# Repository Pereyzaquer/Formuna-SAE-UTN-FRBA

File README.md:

# Fórmula SAE - UTN-FRBA

<p>Este repositorio está destinado al equipo de <strong>Fórmula SAE UTN-FRBA</strong>.<br>
Su objetivo es centralizar y compartir los <strong>esquemáticos</strong>, <strong>código</strong> y <strong>documentación técnica</strong> correspondientes a las distintas áreas del proyecto.</p>

<p>Para consultas, dudas o reportes de problemas, comuníquese con el responsable del área correspondiente.</p>

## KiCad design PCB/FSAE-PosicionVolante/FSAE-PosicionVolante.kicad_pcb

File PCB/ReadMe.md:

# Organización del repositorio

Para mantener un orden y facilitar el trabajo colaborativo, se recomienda seguir las siguientes pautas:

1. **Crear una carpeta por proyecto**, con un nombre descriptivo, para mantener separados los distintos desarrollos.

2. Colocar un ReadMe.md con la organizacion de la carpeta y los integrantes involucrados
3. **Coordinar con el resto del equipo** antes de realizar cambios importantes, para asegurar una correcta integración y evitar conflictos.
4. **Centralizar los símbolos y huellas** en dos carpetas específicas:
   - `Formula_SAE_FP`: destinada a guardar todos los **footprints (huellas)** creados o agregados.  
   - `Formula_SAE_SIM`: destinada a guardar todos los **símbolos esquemáticos** creados o agregados.

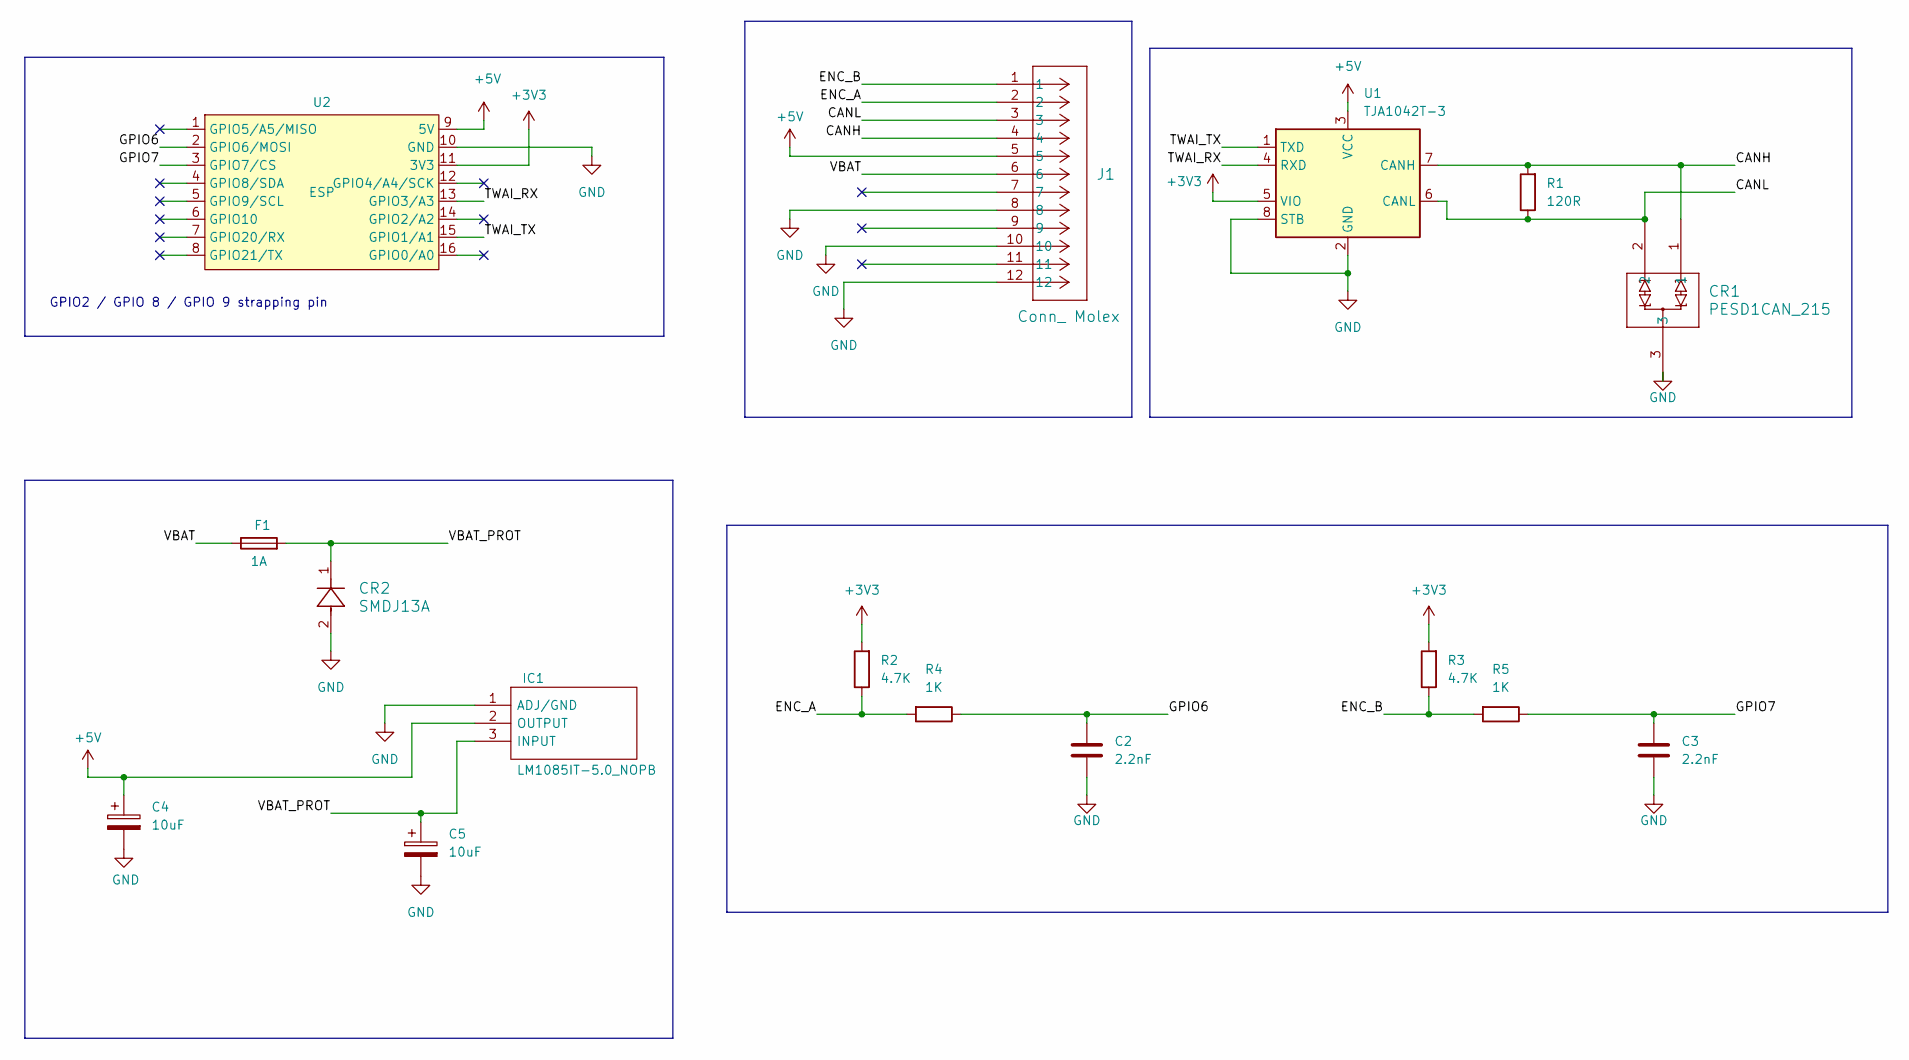
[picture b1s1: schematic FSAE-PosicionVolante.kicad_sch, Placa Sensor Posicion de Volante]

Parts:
C2, C3: 2.2nF; C_0805_2012Metric_Pad1.18x1.45mm_HandSolder
C4: 10uF; CP_EIA-3216-18_Kemet-A_HandSolder
C5: 10uF; C_1206_3216Metric_Pad1.33x1.80mm_HandSolder
CR1: PESD1CAN_215; SOT23_PESD1_NEX
CR2: SMDJ13A; SMDJSeries_LTF
F1: 1A; Fuse_1206_3216Metric_Pad1.42x1.75mm_HandSolder
IC1: LM1085IT-5.0_NOPB; TO254P470X1028X1955-3P; Manufacturer_Part_Number LM1085IT-5.0/NOPB
J1: Conn_ Molex; CONN_3678312xx_MOL
R1: 120R; R_0805_2012Metric_Pad1.20x1.40mm_HandSolder
R2, R3: 4.7K; R_0805_2012Metric_Pad1.20x1.40mm_HandSolder
R4, R5: 1K; R_0805_2012Metric_Pad1.20x1.40mm_HandSolder
U1: TJA1042T-3; SOIC-8_3.9x4.9mm_P1.27mm
U2: ESP; ESP32 C3 SM

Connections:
+3V3: R2.2, R3.2, U1.5 (VIO), U2.11 (3V3)
+5V: C4.1, IC1.2 (OUTPUT), J1.5, U1.3 (VCC), U2.9 (5V)
/CANH: CR1.1, J1.4, R1.2, U1.7 (CANH)
/CANL: CR1.2, J1.3, R1.1, U1.6 (CANL)
/ENC_A: J1.2, R2.1, R4.2
/ENC_B: J1.1, R3.1, R5.2
/GPIO6: C2.1, R4.1, U2.2 (GPIO6/MOSI)
/GPIO7: C3.1, R5.1, U2.3 (GPIO7/CS)
/TWAI_RX: U1.4 (RXD), U2.13 (GPIO3/A3)
/TWAI_TX: U1.1 (TXD), U2.15 (GPIO1/A1)
/VBAT: F1.1, J1.6
/VBAT_PROT: C5.1, CR2.1, F1.2, IC1.3 (INPUT)
GND: C2.2, C3.2, C4.2, C5.2, CR1.3, CR2.2, IC1.1 (ADJ/GND), J1.8, J1.10, J1.12, U1.2 (GND), U1.8 (STB), U2.10 (GND)

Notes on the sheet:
GPIO2 / GPIO 8 / GPIO 9 strapping pin

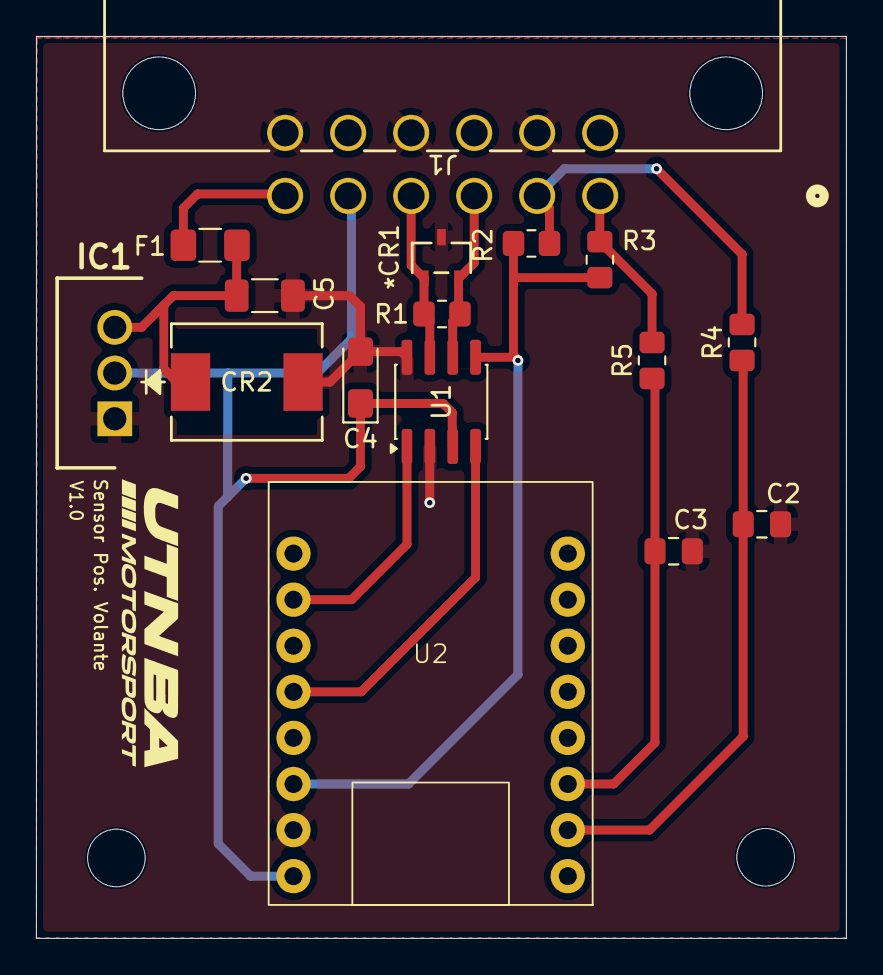
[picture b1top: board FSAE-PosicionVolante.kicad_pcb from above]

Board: 2 copper layers, 45.0 x 50.1 mm, 17 parts (0 on the bottom side), 13 nets.

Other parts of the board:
G: LOGO; logo

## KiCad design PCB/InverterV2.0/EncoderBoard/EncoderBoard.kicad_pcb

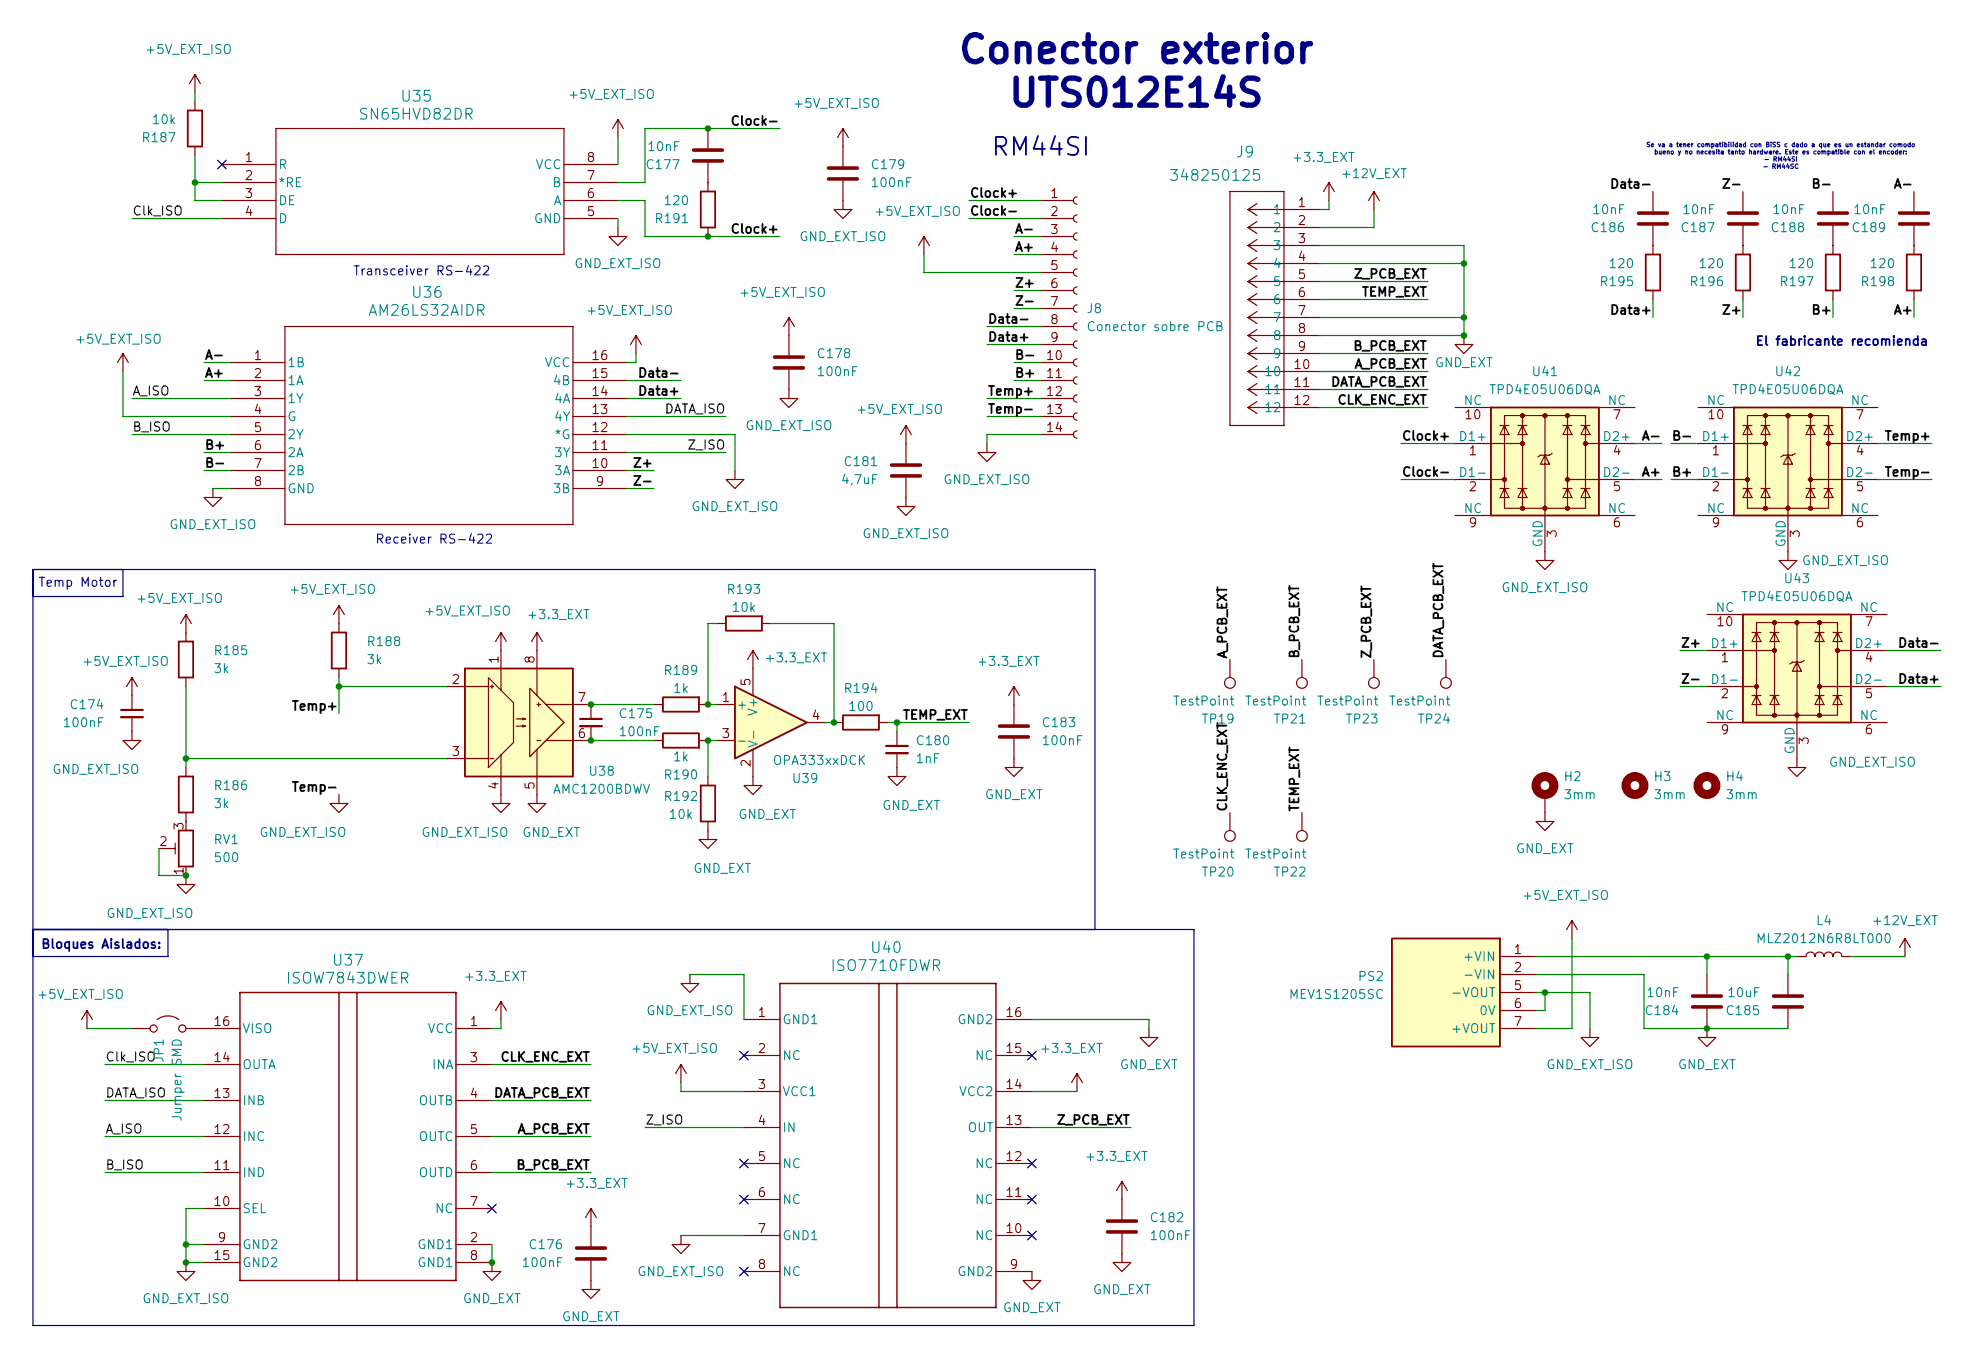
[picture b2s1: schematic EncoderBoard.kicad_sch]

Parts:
C174, C175, C176, C178, C179, C182, C183: 100nF; C_0603_1608Metric
C177, C184, C186, C187, C188, C189: 10nF; C_0603_1608Metric
C180: 1nF; C_0603_1608Metric
C181: 4,7uF; C_0805_2012Metric
C185: 10uF; C_0805_2012Metric
H2: 3mm; MountingHole_3.2mm_M3_ISO14580_Pad_TopBottom
H3, H4: 3mm; MountingHole_3.2mm_M3
J8: Conector sobre PCB; My-UTS012E14S
J9: 348250125; CONN_SD-34825-001_12_MOL
JP1: Jumper SMD; SolderJumper-2_P1.3mm_Open_RoundedPad1.0x1.5mm
L4: MLZ2012N6R8LT000; L_0805_2012Metric
PS2: MEV1S1205SC; MANUFACTURER_PART_NUMBER MEV1S1205SC; Mouser Part Number 580-MEV1S1205SC
R185, R186, R188: 3k; R_0603_1608Metric
R187: 10k; R_0603_1608Metric
R189, R190: 1k; R_0402_1005Metric
R191, R195, R196, R197, R198: 120; R_0603_1608Metric
R192, R193: 10k; R_0402_1005Metric
R194: 100; R_0402_1005Metric
RV1: 500; Potentiometer_Bourns_3296W_Vertical
TP19, TP20, TP21, TP22, TP23, TP24: TestPoint; TestPoint_Pad_D1.0mm
U35: SN65HVD82DR; D8_TEX-L
U36: AM26LS32AIDR; D16-L
U37: ISOW7843DWER; DWE0016A
U38: AMC1200BDWV; SOIC-8_7.5x5.85mm_P1.27mm
U39: OPA333xxDCK; SOT-353_SC-70-5
U40: ISO7710FDWR; SOIC16_DW_TEX-L
U41, U42, U43: TPD4E05U06DQA; USON-10_2.5x1.0mm_P0.5mm

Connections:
+3.3_EXT: C176.1, C182.1, C183.1, J9.1, U37.1 (VCC), U38.8 (VDD2), U39.5 (V+), U40.14 (VCC2)
+5V_EXT_ISO: C174.1, C178.1, C179.1, C181.1, J8.5, JP1.2 (B), PS2.7 (+VOUT), R185.2, R187.2, R188.2, U35.8 (VCC), U36.4 (G), U36.16 (VCC), U38.1 (VDD1), U40.3 (VCC1)
+12V_EXT: J9.2, L4.2
/A+: J8.4, R198.1, U36.2 (1A), U41.5 (D2-)
/A-: C189.1, J8.3, U36.1 (1B), U41.4 (D2+)
/A_ISO: U36.3 (1Y), U37.12 (INC)
/A_PCB_EXT: J9.10, TP19.1 (1_1), U37.5 (OUTC)
/B+: J8.11, R197.1, U36.6 (2A), U42.2 (D1-)
/B-: C188.1, J8.10, U36.7 (2B), U42.1 (D1+)
/B_ISO: U36.5 (2Y), U37.11 (IND)
/B_PCB_EXT: J9.9, TP21.1 (1_1), U37.6 (OUTD)
/CLK_ENC_EXT: J9.12, TP20.1 (1_1), U37.3 (INA)
/Clk_ISO: U35.4 (D), U37.14 (OUTA)
/Clock+: J8.1, R191.1, U35.6 (A), U41.1 (D1+)
/Clock-: C177.1, J8.2, U35.7 (B), U41.2 (D1-)
/DATA_ISO: U36.13 (4Y), U37.13 (INB)
/DATA_PCB_EXT: J9.11, TP24.1 (1_1), U37.4 (OUTB)
/Data+: J8.9, R195.1, U36.14 (4A), U43.5 (D2-)
/Data-: C186.1, J8.8, U36.15 (4B), U43.4 (D2+)
/TEMP_EXT: C180.1, J9.6, R194.2, TP22.1 (1_1)
/Temp+: J8.12, R188.1, U38.2 (VINP), U42.4 (D2+)
/Z+: J8.6, R196.1, U36.10 (3A), U43.1 (D1+)
/Z-: C187.1, J8.7, U36.9 (3B), U43.2 (D1-)
/Z_ISO: U36.11 (3Y), U40.4 (IN)
/Z_PCB_EXT: J9.5, TP23.1 (1_1), U40.13 (OUT)
GND_EXT: C176.2, C180.2, C182.2, C183.2, C184.2, C185.2, H2.1 (1_1), J9.3, J9.4, J9.7, J9.8, PS2.2 (-VIN), R192.1, U37.2 (GND1), U37.8 (GND1), U38.5 (GND2), U39.2 (V-), U40.9 (GND2), U40.16 (GND2)
GND_EXT_ISO: C174.2, C178.2, C179.2, C181.2, J8.13, J8.14, PS2.5 (-VOUT), PS2.6 (0V), RV1.1, RV1.2, U35.5 (GND), U36.8 (GND), U36.12 (*G), U37.9 (GND2), U37.10 (SEL), U37.15 (GND2), U38.4 (GND1), U40.1 (GND1), U40.7 (GND1), U41.3 (GND), U41.8 (GND), U42.3 (GND), U42.5 (D2-), U42.8 (GND), U43.3 (GND), U43.8 (GND)
unnamed: C177.2, R191.2
unnamed: C186.2, R195.2
unnamed: C187.2, R196.2
unnamed: C188.2, R197.2
unnamed: C189.2, R198.2
unnamed: JP1.1 (A), U37.16 (VISO)
unnamed: C184.1, C185.1, L4.1, PS2.1 (+VIN)
unnamed: R186.1, RV1.3
unnamed: R193.2, R194.1, U39.4
unnamed: R187.1, U35.2 (*RE), U35.3 (DE)
unnamed: R185.1, R186.2, U38.3 (VINN)
unnamed: C175.2, R190.1, U38.6 (VOUTN)
unnamed: C175.1, R189.1, U38.7 (VOUTP)
unnamed: R189.2, R193.1, U39.1 (+)
unnamed: R190.2, R192.2, U39.3 (-)

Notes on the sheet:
Conector exterior UTS012E14S
Receiver RS-422
Temp Motor
Transceiver RS-422
Se va a tener compatibilidad con BiSS c dado a que es un estandar comodo bueno y no necesita tanto hardware. Este es compatible con el encoder: - RM44SI - RM44SC
Bloques Aislados:
RM44SI
El fabricante recomienda

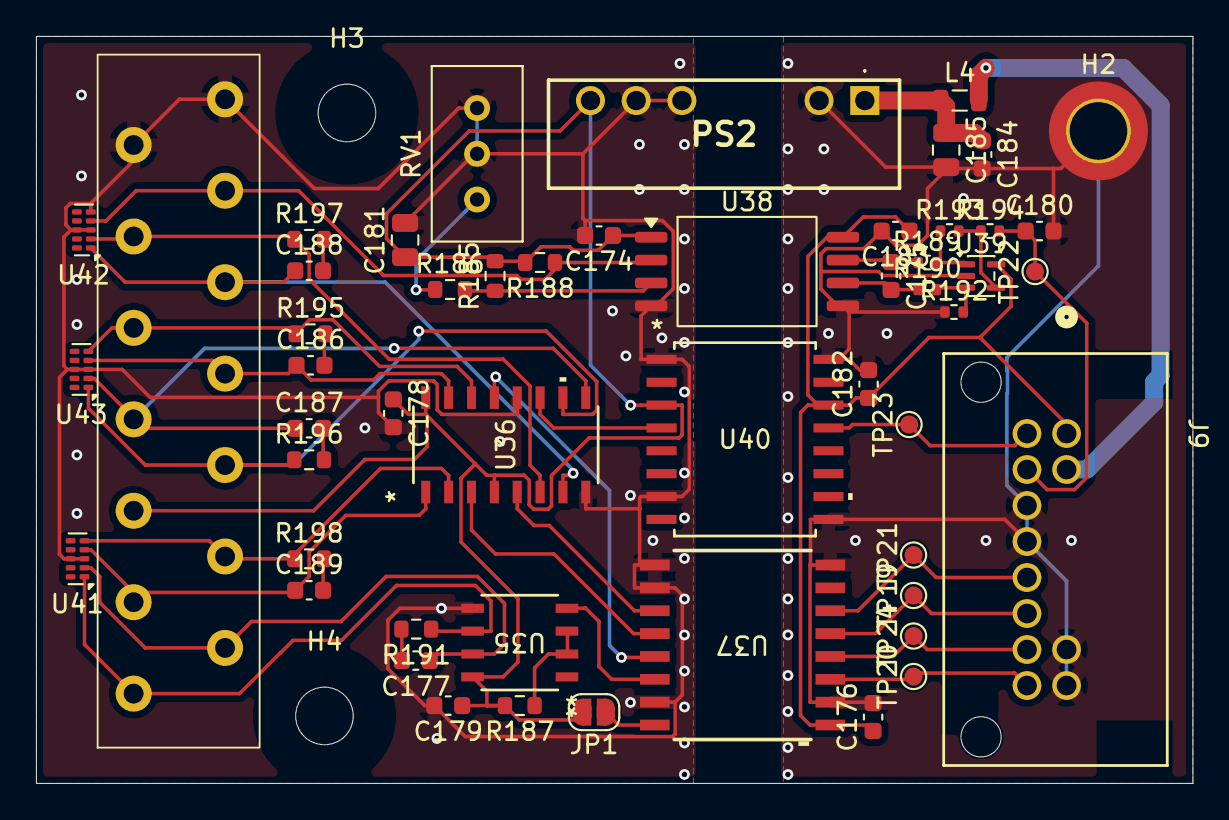
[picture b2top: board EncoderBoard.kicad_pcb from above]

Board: 2 copper layers, 64.2 x 41.5 mm, 54 parts (0 on the bottom side), 42 nets.

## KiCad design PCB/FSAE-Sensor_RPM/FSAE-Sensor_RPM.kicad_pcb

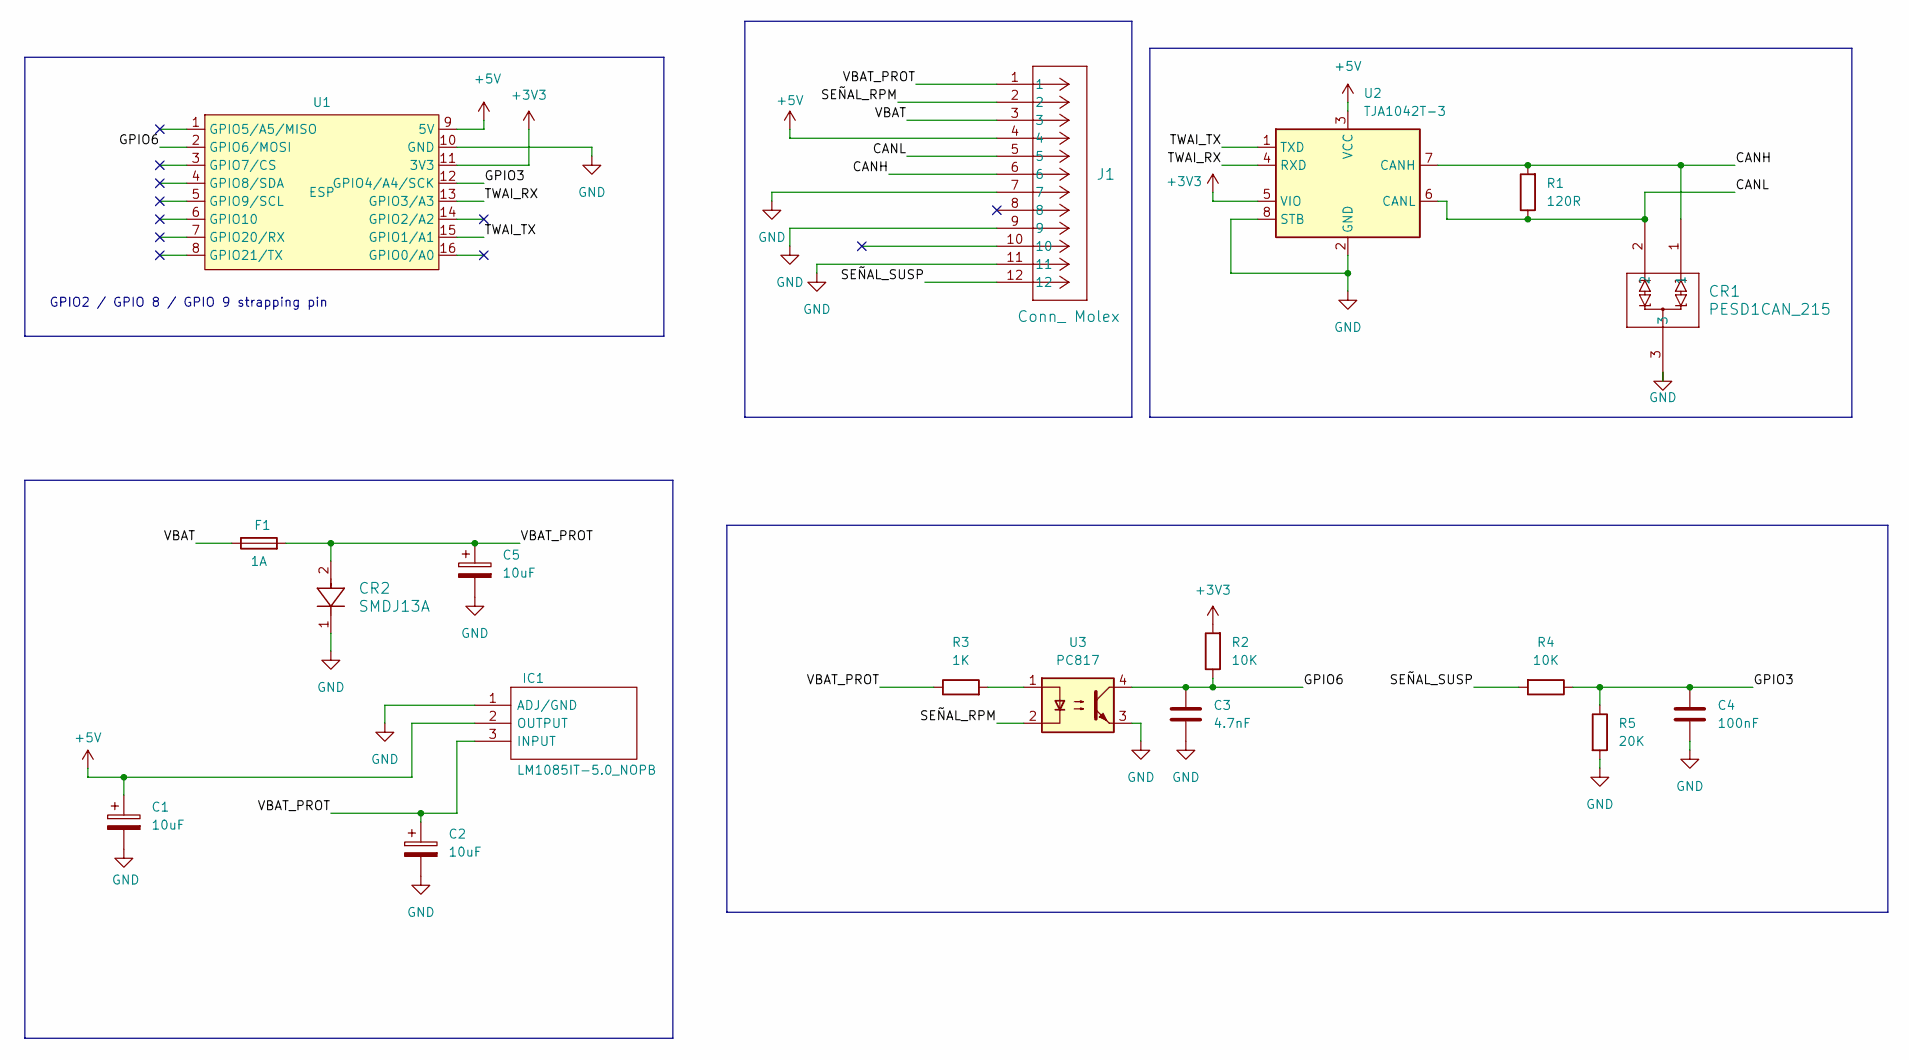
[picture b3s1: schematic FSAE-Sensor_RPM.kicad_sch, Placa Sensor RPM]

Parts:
C1: 10uF; CP_EIA-2012-12_Kemet-R_HandSolder
C2, C5: 10uF; C_0805_2012Metric_Pad1.18x1.45mm_HandSolder
C3: 4.7nF; C_0805_2012Metric_Pad1.18x1.45mm_HandSolder
C4: 100nF; C_0805_2012Metric_Pad1.18x1.45mm_HandSolder
CR1: PESD1CAN_215; SOT23_PESD1_NEX
CR2: SMDJ13A; SMDJSeries_LTF
F1: 1A; Fuse_1206_3216Metric_Pad1.42x1.75mm_HandSolder
IC1: LM1085IT-5.0_NOPB; TO254P470X1028X1955-3P; Manufacturer_Part_Number LM1085IT-5.0/NOPB
J1: Conn_ Molex; CONN_3678312xx_MOL
R1: 120R; R_0805_2012Metric_Pad1.20x1.40mm_HandSolder
R2, R4: 10K; R_0805_2012Metric_Pad1.20x1.40mm_HandSolder
R3: 1K; R_0805_2012Metric_Pad1.20x1.40mm_HandSolder
R5: 20K; R_0805_2012Metric_Pad1.20x1.40mm_HandSolder
U1: ESP; ESP32 C3 SM
U2: TJA1042T-3; SOIC-8_3.9x4.9mm_P1.27mm
U3: PC817; DIP-4_W7.62mm

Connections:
+3V3: R2.2, U1.11 (3V3), U2.5 (VIO)
+5V: C1.1, IC1.2 (OUTPUT), J1.4, U1.9 (5V), U2.3 (VCC)
/CANH: CR1.1, J1.6, R1.2, U2.7 (CANH)
/CANL: CR1.2, J1.5, R1.1, U2.6 (CANL)
/GPIO3: C4.1, R4.1, R5.1, U1.12 (GPIO4/A4/SCK)
/GPIO6: C3.1, R2.1, U1.2 (GPIO6/MOSI), U3.4
/SEÑAL_RPM: J1.2, U3.2
/SEÑAL_SUSP: J1.12, R4.2
/TWAI_RX: U1.13 (GPIO3/A3), U2.4 (RXD)
/TWAI_TX: U1.15 (GPIO1/A1), U2.1 (TXD)
/VBAT: F1.1, J1.3
/VBAT_PROT: C2.1, C5.1, CR2.2, F1.2, IC1.3 (INPUT), J1.1, R3.1
GND: C1.2, C2.2, C3.2, C4.2, C5.2, CR1.3, CR2.1, IC1.1 (ADJ/GND), J1.7, J1.9, J1.11, R5.2, U1.10 (GND), U2.2 (GND), U2.8 (STB), U3.3
unnamed: R3.2, U3.1

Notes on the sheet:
GPIO2 / GPIO 8 / GPIO 9 strapping pin

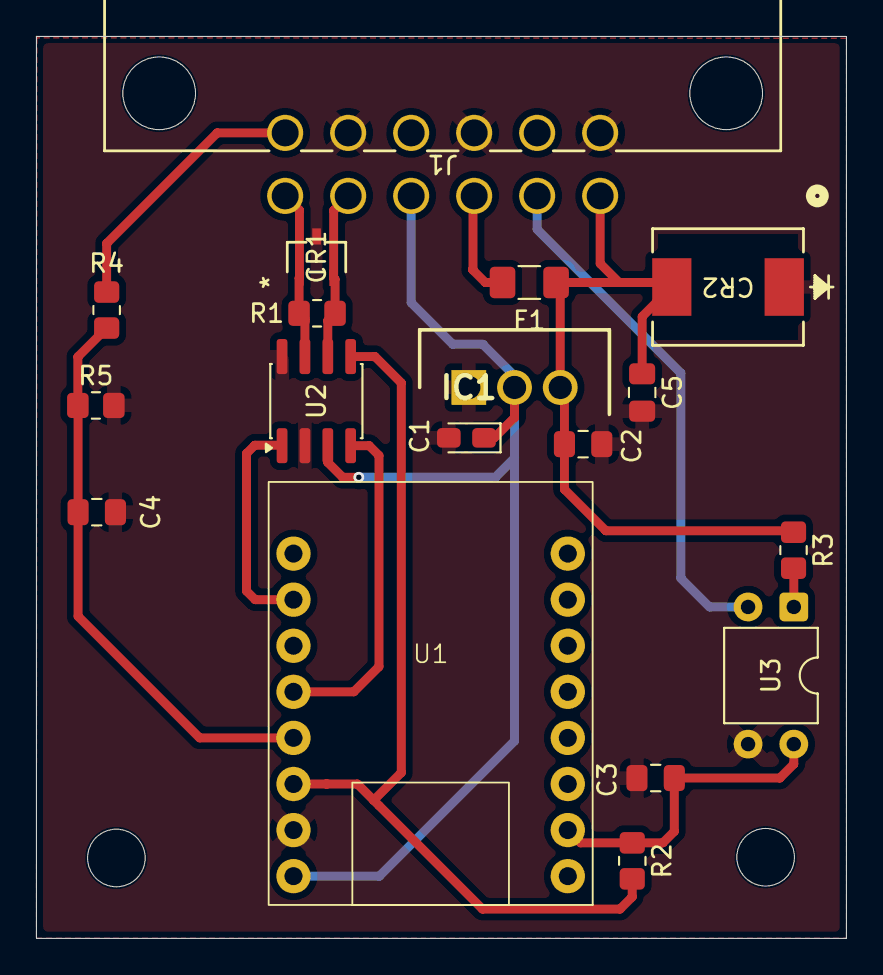
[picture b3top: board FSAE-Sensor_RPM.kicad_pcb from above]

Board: 2 copper layers, 45.0 x 50.1 mm, 18 parts (0 on the bottom side), 14 nets.

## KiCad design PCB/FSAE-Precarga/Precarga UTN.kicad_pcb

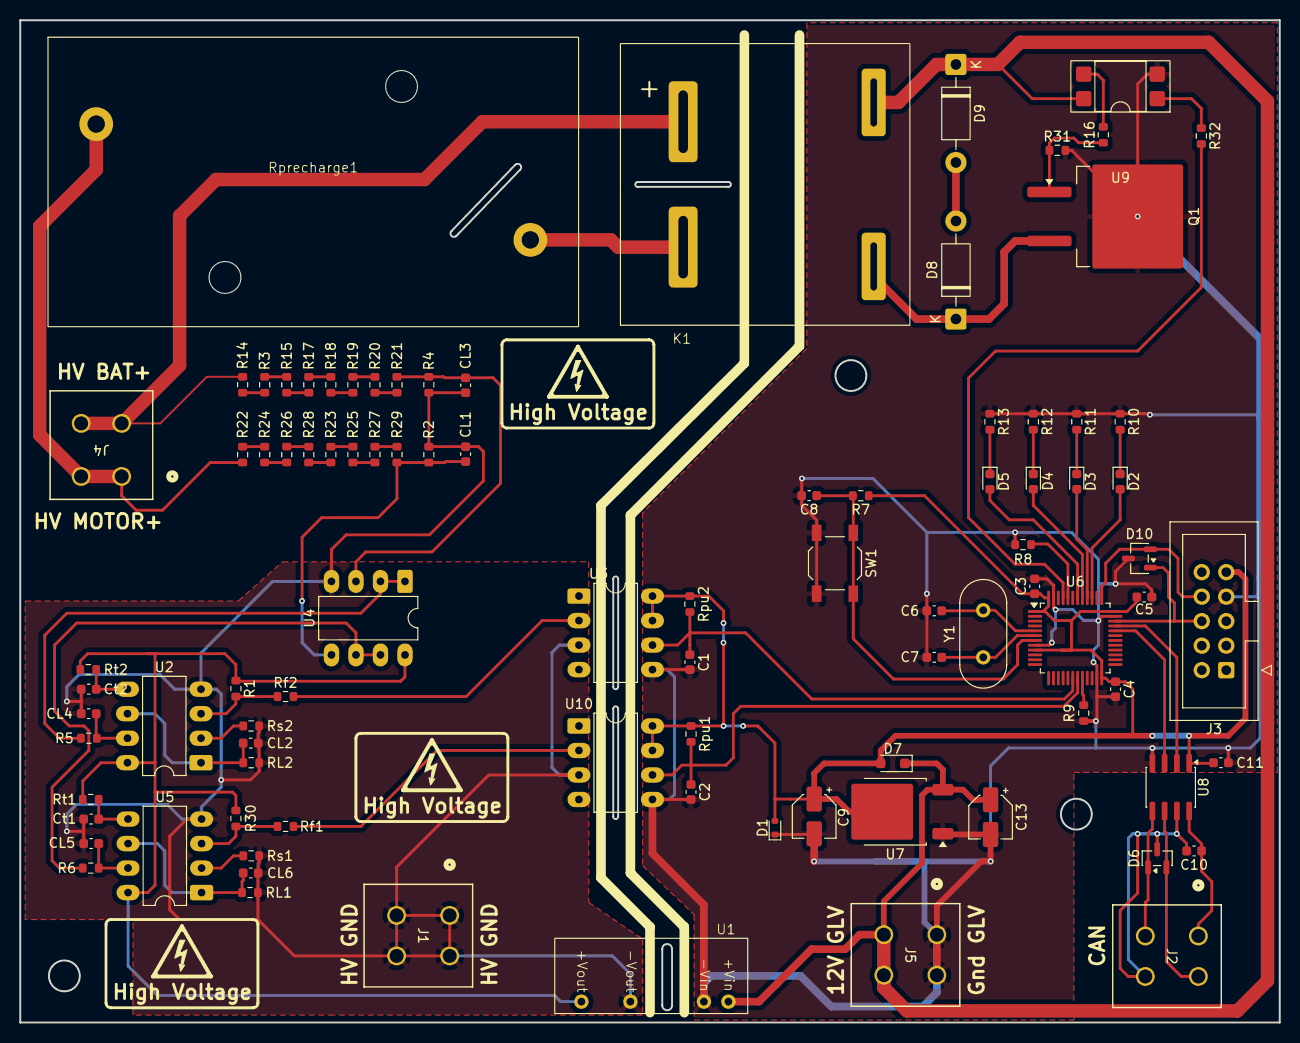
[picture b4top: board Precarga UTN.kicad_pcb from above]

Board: 2 copper layers, 130.6 x 103.9 mm, 92 parts (0 on the bottom side), 67 nets.

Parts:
C1, C2: 10p; C_0603_1608Metric
C3, C4, C5, C8, C10, C11: 100n; C_0603_1608Metric
C6, C7: 20p; C_0603_1608Metric
C9, C13: 10u; CP_Elec_4x5.4
CL1, CL2, CL3, CL4, CL5, CL6: 10n; C_0603_1608Metric
Ct1, Ct2: 4.7n; C_0603_1608Metric
D1: BSD5C031V; D_SOD-523
D2, D4: LED_Verde; LED_0603_1608Metric
D3: LED_Amarillo; LED_0603_1608Metric
D5: LED_Rojo; LED_0603_1608Metric
D6: NUP2105L; SOT-23
D7: 1N4148W; D_SOD-323_HandSoldering
D8: 1N5363; D_DO-41_SOD81_P10.16mm_Horizontal
D9: SB5100; D_DO-41_SOD81_P10.16mm_Horizontal
D10: ESDA5V3L; SOT-23-3
J1, J2, J4, J5: 39310040; CONN_SD-5566-002_04_MOL
J3: Programming Port; IDC-Header_2x05_P2.54mm_Vertical
K1: RER02; RER02PAX
Q1: IRF640S; TO-263-2
R1, R5, R6, R7, R8, R9, R30: 10k; R_0603_1608Metric
R2, R4: 5k; R_0603_1608Metric
R3, R14, R15, R17, R18, R19, R20, R21, R22, R23, R24, R25, R26, R27, R28, R29: 49.9k; R_0603_1608Metric
R10, R11, R12, R13: 220; R_0603_1608Metric
R16, R32: 1k; R_0603_1608Metric
R31: 100k; R_0603_1608Metric
RL1, RL2: 10k; R_0603_1608Metric
Rf1, Rf2: 2.2k; R_0603_1608Metric
Rprecharge1: 470; HS25 470R F
Rpu1, Rpu2: 1k; R_0603_1608Metric
Rs1, Rs2: 10k; R_0603_1608Metric
Rt1, Rt2: 6.8k; R_0603_1608Metric
SW1: SW_MEC_5E; SW_SPST_TL3342
U1: NMK0512SAC
U2, U5: LM331N; DIP-8_W7.62mm_LongPads
U3, U10: 6N137; DIP-8_W7.62mm_LongPads
U4: LM2904; DIP-8_W7.62mm_LongPads
U6: STM32F103C8Tx; LQFP-48_7x7mm_P0.5mm
U7: LM1117DT-3.3; TO-252-2
U8: ISO1044BD; SOIC-8_3.9x4.9mm_P1.27mm
U9: PC817; DIP-4_W7.62mm_SMDSocket_SmallPads
Y1: Crystal; Crystal_HC49-4H_Vertical

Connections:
3.3V_GLV: C3.1, C4.1, C5.1, C9.1, C11.1, D1.2 (A2), D7.2 (A), J3.9, R7.1, Rpu1.1, Rpu2.1, U3.7 (EN), U3.8 (VCC), U6.1 (VBAT), U6.9 (VDDA), U6.24 (VDD), U6.36 (VDD), U6.48 (VDD), U7.2 (VO), U8.1 (VCC1), U10.7 (EN), U10.8 (VCC)
12V_GLV: C13.1, D7.1 (K), D9.1 (K), J5.3, J5.4, K1.X1, U1.1 (+Vin), U7.3 (VI), U9.4
12V_TS: R1.1, R30.1, Rt1.1, Rt2.1, U1.7 (+Vout), U2.8 (VS), U4.8 (V+), U5.8 (VS)
/CAN/CAN_H: D6.2 (K), J2.2, U8.6 (CANH)
/CAN/CAN_L: D6.1 (K), J2.3, U8.5 (CANL)
/CAN/Gnd2: C10.2, D6.3 (A), J2.4, U8.7 (GND2)
/CAN/Vcc2: C10.1, J2.1, U8.8 (VCC2)
/VRprec+: J4.3, J4.4, K1.A1+, R14.1
/VRprec-: J4.1, J4.2, R22.1, Rprecharge1.1
Boot0: R8.2, U6.44 (BOOT0)
Boot1: R9.2, U6.20 (PB2)
CAN_Rx: U6.32 (PA11), U8.3 (RXD)
CAN_Tx: U6.33 (PA12), U8.2 (TXD)
Gnd_GLV: C1.2, C2.2, C3.2, C4.2, C5.2, C6.1, C7.1, C8.2, C9.2, C11.2, C13.2, D1.1 (A1), D10.3 (A), J3.7, J5.1, J5.2, Q1.2 (S), R8.1, R9.1, R10.1, R11.1, R12.1, R13.1, R31.2, SW1.3 (K), SW1.4 (A), U1.2 (-Vin), U3.5 (GND), U6.8 (VSSA), U6.23 (VSS), U6.35 (VSS), U6.47 (VSS), U7.1 (GND), U8.4 (GND1), U9.2, U10.5 (GND)
Gnd_TS: CL1.2, CL2.2, CL3.2, CL4.2, CL5.2, CL6.2, Ct1.2, Ct2.2, J1.1, J1.2, J1.3, J1.4, R2.2, R4.2, RL1.2, RL2.2, Rs1.2, Rs2.2, U1.5 (-Vout), U2.4 (GND), U3.3 (C), U4.4 (V-), U5.4 (GND), U10.3 (C)
LogicSigPrec+: C1.1, Rpu2.2, U3.6 (VO), U6.18 (PB0)
LogicSigPrec-: C2.1, Rpu1.2, U6.19 (PB1), U10.6 (VO)
unnamed: D2.1 (K), R10.2
unnamed: D3.1 (K), R11.2
unnamed: D4.1 (K), R12.2
unnamed: D5.1 (K), R13.2
unnamed: D8.2 (A), D9.2 (A)
unnamed: D8.1 (K), K1.X2, Q1.3 (D)
unnamed: K1.A2-, Rprecharge1.2
unnamed: Q1.1 (G), R16.1, R31.1
unnamed: R3.1, R14.2
unnamed: R3.2, R15.1
unnamed: R15.2, R17.1
unnamed: R16.2, U9.3
unnamed: R17.2, R18.1
unnamed: R18.2, R19.1
unnamed: R19.2, R20.1
unnamed: R20.2, R21.1
unnamed: R22.2, R24.1
unnamed: R23.1, R28.2
unnamed: R23.2, R25.1
unnamed: R24.2, R26.1
unnamed: R25.2, R27.1
unnamed: R26.2, R28.1
unnamed: R27.2, R29.1
unnamed: R32.1, U9.1
unnamed: CL4.1, R5.2, U2.7 (COMPIN)
unnamed: R1.2, Rf2.1, U2.3 (FOUT)
unnamed: CL2.1, RL2.1, U2.1 (IOUT), U2.6 (THRESH)
unnamed: Rs2.1, U2.2 (IREF)
unnamed: Ct2.1, Rt2.2, U2.5 (RC)
unnamed: Rf2.2, U3.2 (A)
unnamed: CL3.1, R4.1, R21.2, U4.3 (+)
unnamed: R5.1, U4.1, U4.2 (-)
unnamed: CL1.1, R2.1, R29.2, U4.5 (+)
unnamed: R6.1, U4.6 (-), U4.7
unnamed: CL5.1, R6.2, U5.7 (COMPIN)
unnamed: R30.2, Rf1.1, U5.3 (FOUT)
unnamed: CL6.1, RL1.1, U5.1 (IOUT), U5.6 (THRESH)
unnamed: Rs1.1, U5.2 (IREF)
unnamed: Ct1.1, Rt1.2, U5.5 (RC)
unnamed: Rf1.2, U10.2 (A)
OSC_In: C6.2, U6.5 (PD0), Y1.2
OSC_Out: C7.2, U6.6 (PD1), Y1.1
PCH: R32.2, U6.45 (PB8)
RESET_uC: C8.1, R7.2, SW1.1, SW1.2, U6.7 (NRST)
SW_Clk: D10.2 (K), J3.8, U6.37 (PA14)
SW_DIO: D10.1 (K), J3.6, U6.34 (PA13)
led0: D2.2 (A), U6.39 (PB3)
led1: D3.2 (A), U6.40 (PB4)
led2: D4.2 (A), U6.41 (PB5)
led3: D5.2 (A), U6.42 (PB6)
